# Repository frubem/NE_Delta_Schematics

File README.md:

# Nuova Elettronica DELTA computer - Redux

## DISCLAIMER

Any use of this project is **under your own responsibility**.
By using this project You will agree that I cannot be held responsible if it will destroy any of your devices, damage your computer, burn down your house or whatever.

### Sponsorship

This project is sponsored by [PCBWay](https://pcbway.com).
PCBWay specializes in manufacturing high-quality PCBs and makes them affordable to hobbyist and professionals alike.

The range of services they offer include PCB prototyping, assembly, instant quotes for your order, a verification process by a team
of experts and an easy to use, hassle-free order process.

I'm grateful to PCBWay for their support in developing this board. It was invaluable, and, thanks to them and thanks to the people that supported me, I was able to push this forward and create the first revision of the DELTA Redux!

## Introduction

This repository contains a recreation of the schematics and PCBs for the DELTA computer, an Apple IIe clone by Nuova Elettronica.

The schematics have been reconstructed starting from the originals found in the Nuova Elettronica magazine (scans included in the repository)
and have been corrected comparing them to scans of the original PCBs, while a new PCB was redrawn.

The files in the `PLDs_ROMs` directory have been provided by Roberto Bazzano, that also uploaded all the available documentation about the DELTA [on his website](https://www.z80ne.com/delta).
His page includes the original schematic scanned from the magazine, the EPROM/PLD dumps, gerbers for two of the boards plus high resolution scans of the PCBs.

This project aims at the following:
1. Recreate the schematics of the main DELTA boards, so they are searchable and easier to use for troubleshooting
2. Rebuild the PCBs using KiCAD, possibly using footprints for easier to find connectors and transistors, and to allow further modifications of the project should someone wish to do so

**Many thanks to Roberto** because, without him, all the effort in recreating the schematics would have been moot!

### Compatibility

The [original article](Docs/delta_computer.pdf) by Nuova Elettronica touts "perfect compatibility with APPLE 2 and APPLE 2E", but I've found out that this is not really the case.

You can reference [this file](Apple2e_differences.md) for differences (and fixes) I found when comparing to an Apple IIe.

Also, note that this clone, by default, boots in 50Hz mode. 60Hz mode can be obtained by properly setting up the CRTC. I have prepared a modified EP780/A ROM for this, you can find it [here](PLDs_ROMs/DELTA_Mainboard/mod/EP780A_60hz.BIN).

Getting the //e enhanced ROMs to work was also easy enough, as it was sufficient to add the CRTC initialization code and the call to it. Note that the VIDEO ROM was not ported over, as the organization of that
ROM on the delta is totally different. Given that I actually plan to evolve this computer using an A2DVI as video circuitry, this should be a non-issue.

### Support

If you wish to support me in building new hardware and software for old machines, [throw a few euros in my direction via Ko-Fi](https://ko-fi.com/hkzlab) ☕!

## Build one!

### Order the PCBs

You can find the gerbers in this repository, or you can order the PCBs at **PCBWay!**

Note that you will need, at least, the motherboard (LX780) and one of the video modules. The keyboard is currently work in progress.

- [LX780](https://www.pcbway.com/project/shareproject/DELTA_Redux_Apple_IIe_clone_dc32412e.html), the motherboard
- [LX782](https://www.pcbway.com/project/shareproject/DELTA_Redux_Composite_TV_Video_card_8b8ff858.html), monochrome composite/VHF video output
- [LX783](https://www.pcbway.com/project/shareproject/DELTA_Redux_RGB_Video_card_4a65742e.html), analog RGB video output

### Fixes

Every board directory contains a `fixes.md` file detailing the fix to apply to each revision of the boards:

- [LX780](LX780_Delta-original/fixes.md)
- [LX782](LX782_Monochrome_Video/fixes.md)
- LX783

### Bill of Material

Every board directory contains a `bom.md` file containing the bill of material for the card.

- [LX780](LX780_Delta-original/bom.md)
- [LX782](LX782_Monochrome_Video/bom.md)
- [LX783](LX783_RGB_Video/bom.md)

## TODO

- Explore the functional differences with an original Apple IIe
- Build a keyboard
- Build a case
- Investigate replacing the video circuitry with an embedded A2DVI board
- Test cassette IN/OUT
- Modify //e enhanced ROMs self test to match behavior of DELTA ROMs

## Thanks

- [Roberto Bazzano](https://www.z80ne.com/) for the photos and PLD dumps
- [DosFox](https://tech.lgbt/@DosFox) for the support

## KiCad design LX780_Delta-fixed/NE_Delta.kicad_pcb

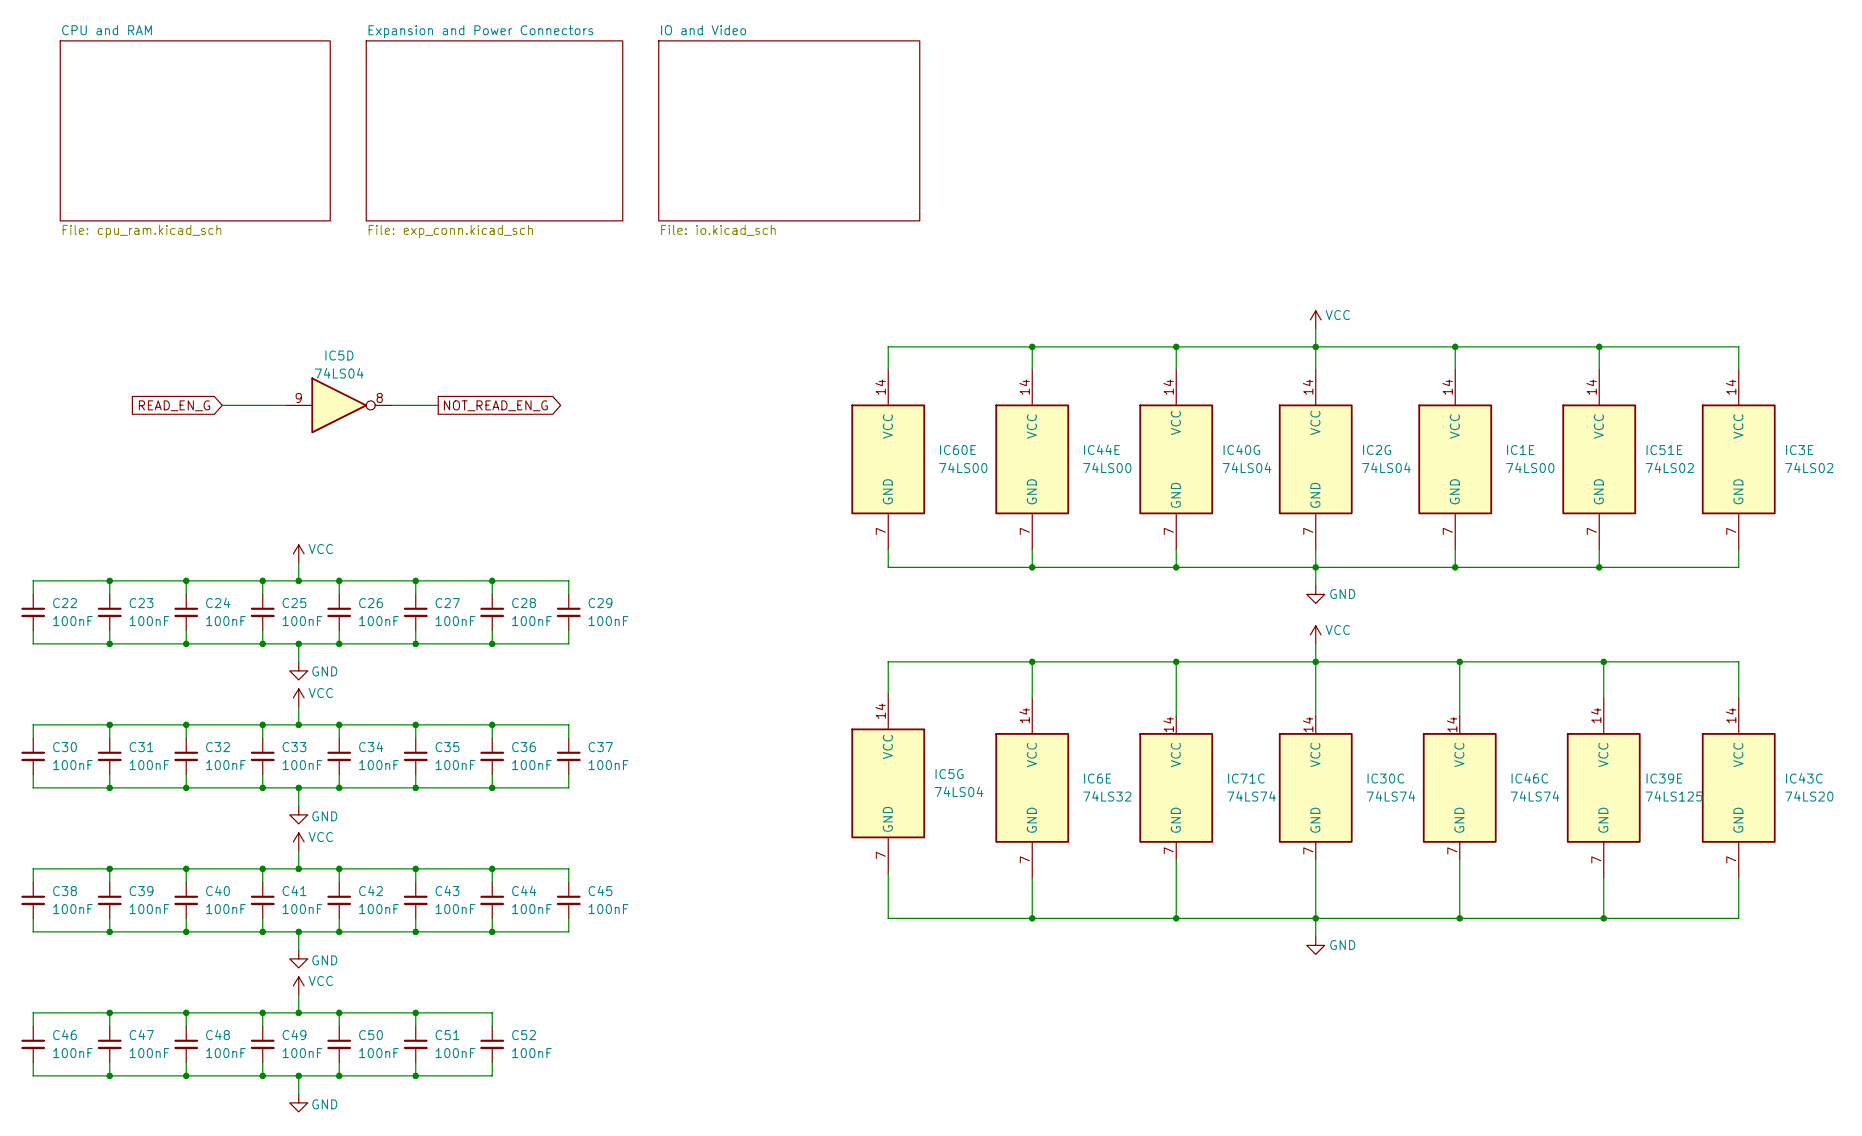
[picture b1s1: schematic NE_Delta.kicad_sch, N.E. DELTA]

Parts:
C22, C23, C24, C25, C26, C27, C28, C29, C30, C31, C32, C33, C34, C35, C36, C37, C38, C39, C40, C41, C42, C43, C44, C45, C46, C47, C48, C49, C50, C51, C52: 100nF; C_Disc_D6.0mm_W2.5mm_P5.00mm
IC1, IC44, IC60: 74LS00; DIP-14_W7.62mm
IC2, IC5, IC40: 74LS04; DIP-14_W7.62mm
IC3, IC51: 74LS02; DIP-14_W7.62mm
IC6: 74LS32; DIP-14_W7.62mm
IC30, IC46, IC71: 74LS74; DIP-14_W7.62mm
IC39: 74LS125; DIP-14_W7.62mm
IC43: 74LS20; DIP-14_W7.62mm

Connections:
+5V: C22.1, C23.1, C24.1, C25.1, C26.1, C27.1, C28.1, C29.1, C30.1, C31.1, C32.1, C33.1, C34.1, C35.1, C36.1, C37.1, C38.1, C39.1, C40.1, C41.1, C42.1, C43.1, C44.1, C45.1, C46.1, C47.1, C48.1, C49.1, C50.1, C51.1, C52.1, IC1.14 (VCC), IC2.14 (VCC), IC3.14 (VCC), IC5.14 (VCC), IC6.14 (VCC), IC30.14 (VCC), IC39.14 (VCC), IC40.14 (VCC), IC43.14 (VCC), IC44.14 (VCC), IC46.14 (VCC), IC51.14 (VCC), IC60.14 (VCC), IC71.14 (VCC); also elsewhere on the board
GND: C22.2, C23.2, C24.2, C25.2, C26.2, C27.2, C28.2, C29.2, C30.2, C31.2, C32.2, C33.2, C34.2, C35.2, C36.2, C37.2, C38.2, C39.2, C40.2, C41.2, C42.2, C43.2, C44.2, C45.2, C46.2, C47.2, C48.2, C49.2, C50.2, C51.2, C52.2, IC1.7 (GND), IC2.7 (GND), IC3.7 (GND), IC5.7 (GND), IC6.7 (GND), IC30.7 (GND), IC39.7 (GND), IC40.7 (GND), IC43.7 (GND), IC44.7 (GND), IC46.7 (GND), IC51.7 (GND), IC60.7 (GND), IC71.7 (GND); also elsewhere on the board
unnamed 261: IC5.8; also elsewhere on the board

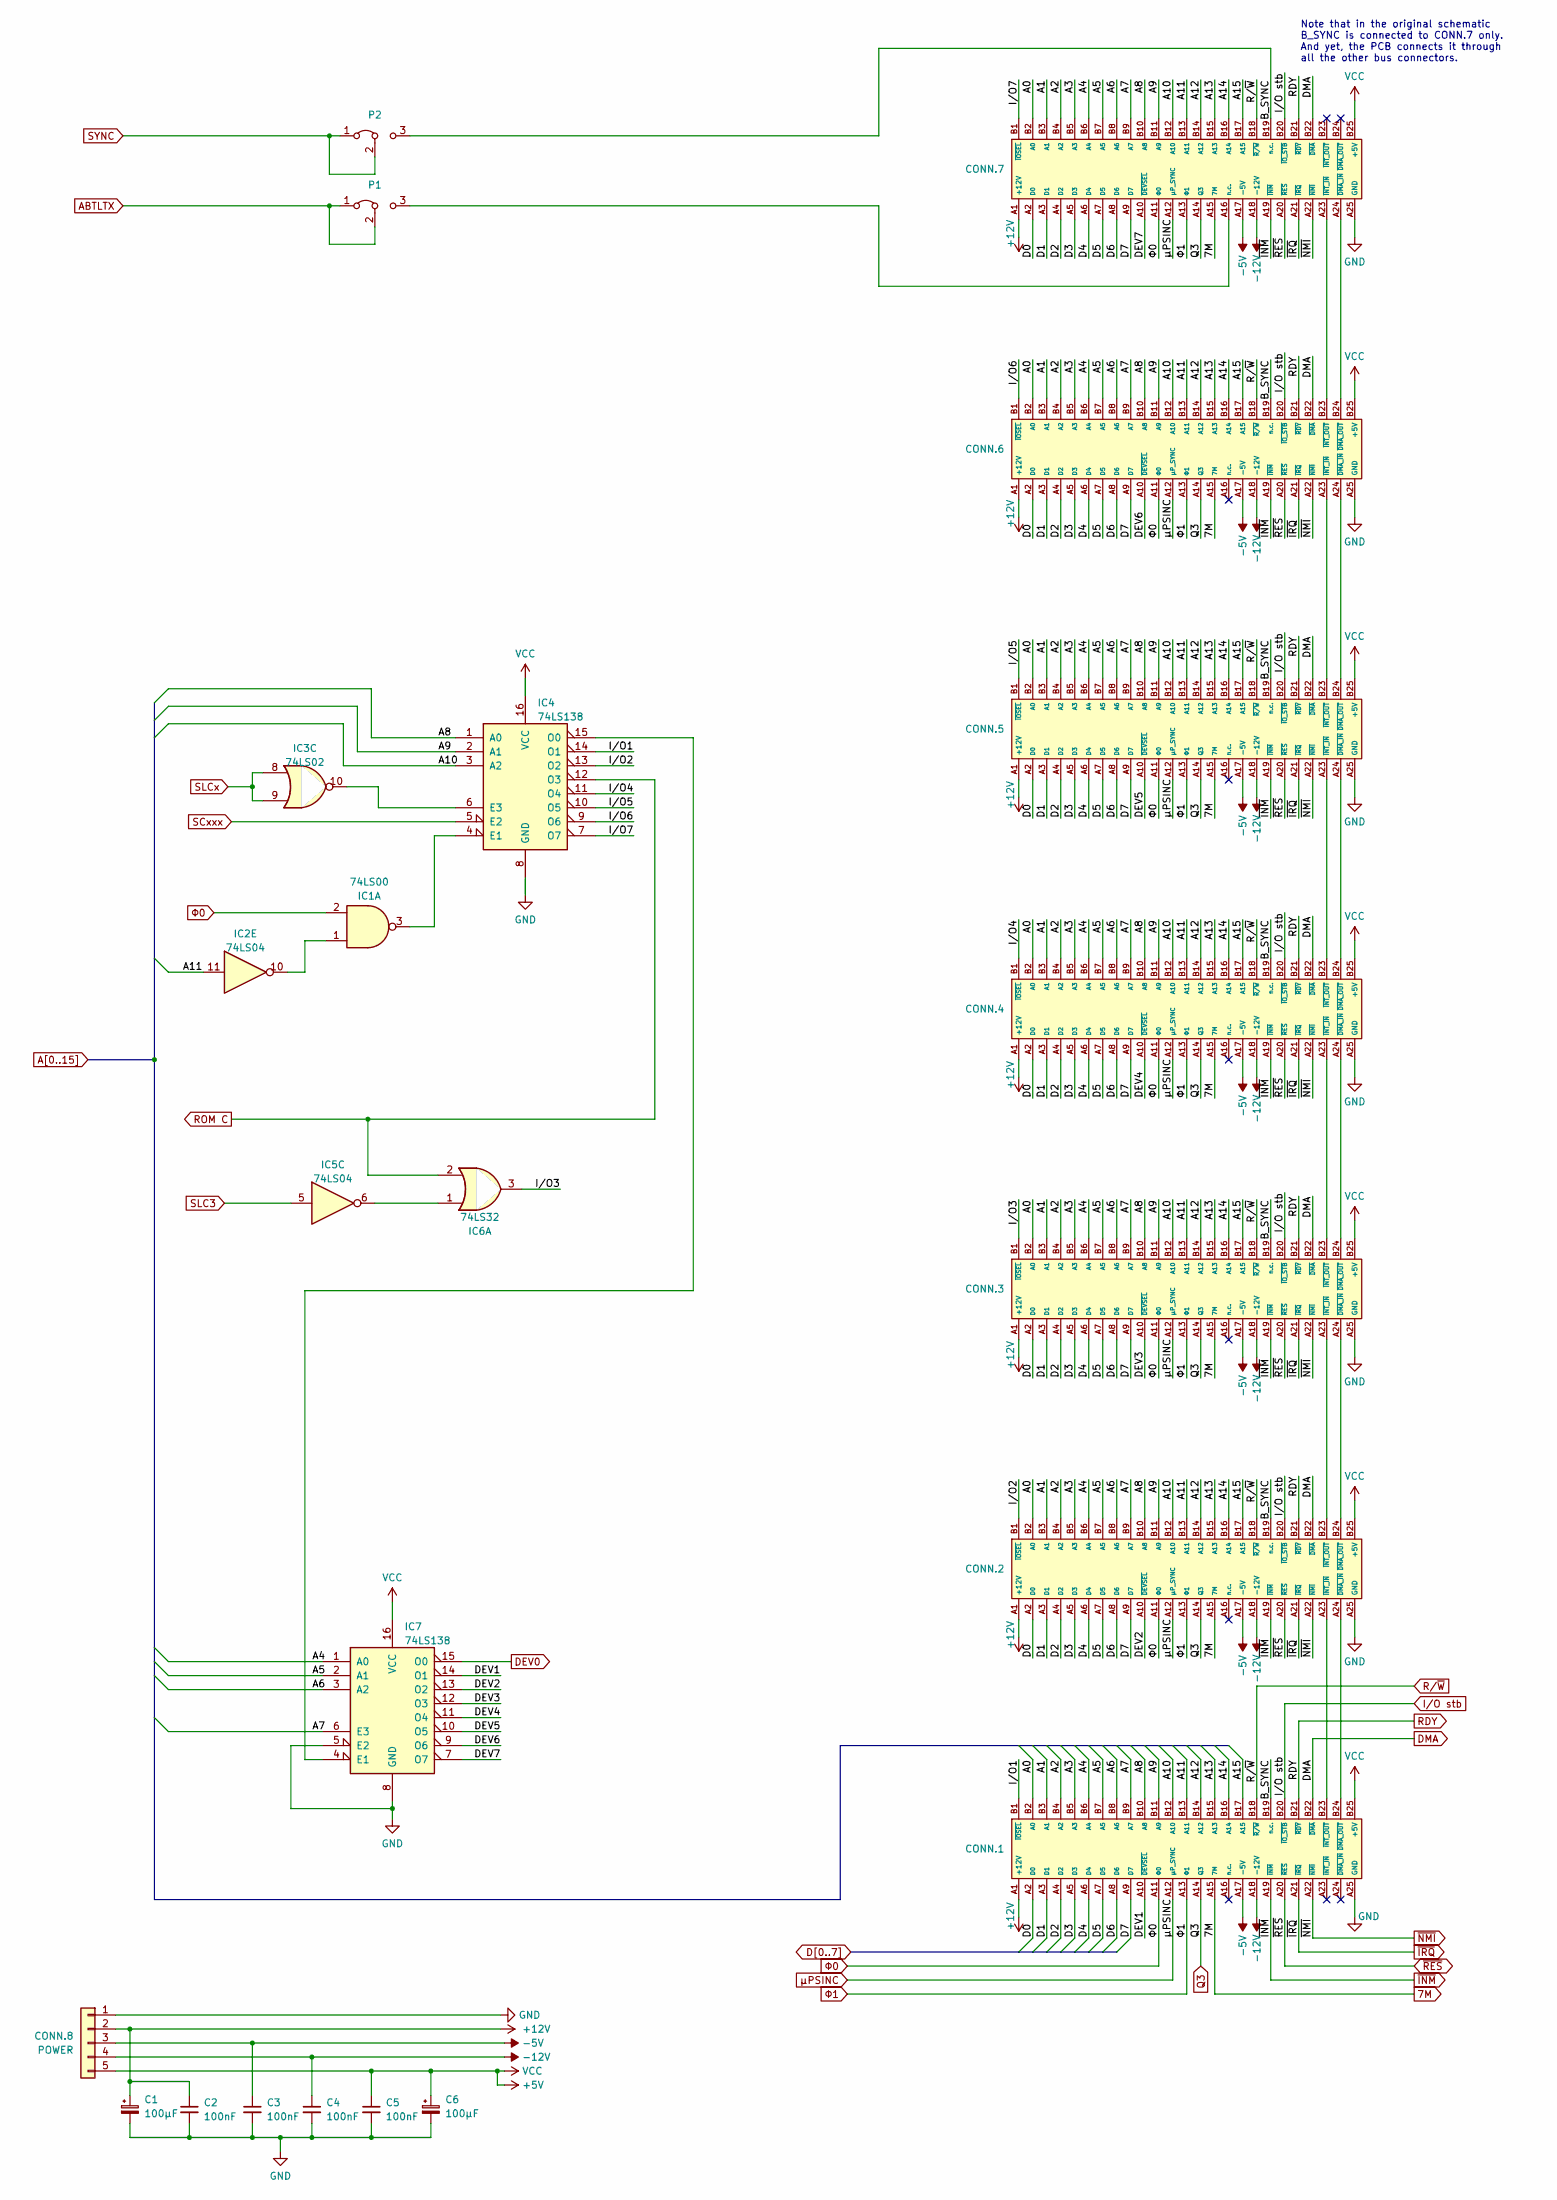
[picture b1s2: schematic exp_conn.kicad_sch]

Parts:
C1, C6: 100μF; CP_Radial_D8.0mm_P5.00mm
C2, C3, C4, C5: 100nF; C_Disc_D6.0mm_W2.5mm_P5.00mm
CONN.1, CONN.2, CONN.3, CONN.4, CONN.5, CONN.6: NE_BUS
CONN.7: NE_BUS_halfsilk
CONN.8: POWER; NE_POWER
IC1: 74LS00; DIP-14_W7.62mm
IC2, IC5: 74LS04; DIP-14_W7.62mm
IC3: 74LS02; DIP-14_W7.62mm
IC4, IC7: 74LS138; DIP-16_W7.62mm
IC6: 74LS32; DIP-14_W7.62mm
P1, P2: Jumper_3_Bridged12; PinHeader_1x03_P2.54mm_Vertical

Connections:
7M: CONN.1.A15 (7M), CONN.2.A15 (7M), CONN.3.A15 (7M), CONN.4.A15 (7M), CONN.5.A15 (7M), CONN.6.A15 (7M), CONN.7.A15 (7M); also elsewhere on the board
+5V: C5.1, C6.1, CONN.1.B25 (+5V), CONN.2.B25 (+5V), CONN.3.B25 (+5V), CONN.4.B25 (+5V), CONN.5.B25 (+5V), CONN.6.B25 (+5V), CONN.7.B25 (+5V), CONN.8.5, IC4.16 (VCC), IC7.16 (VCC); also elsewhere on the board
+12V: C1.1, C2.1, CONN.1.A1 (+12V), CONN.2.A1 (+12V), CONN.3.A1 (+12V), CONN.4.A1 (+12V), CONN.5.A1 (+12V), CONN.6.A1 (+12V), CONN.7.A1 (+12V), CONN.8.2; also elsewhere on the board
-5V: C3.1, CONN.1.A17 (-5V), CONN.2.A17 (-5V), CONN.3.A17 (-5V), CONN.4.A17 (-5V), CONN.5.A17 (-5V), CONN.6.A17 (-5V), CONN.7.A17 (-5V), CONN.8.3; also elsewhere on the board
-12V: C4.1, CONN.1.A18 (-12V), CONN.2.A18 (-12V), CONN.3.A18 (-12V), CONN.4.A18 (-12V), CONN.5.A18 (-12V), CONN.6.A18 (-12V), CONN.7.A18 (-12V), CONN.8.4; also elsewhere on the board
/Expansion and Power Connectors/B_SYNC: CONN.1.B19 (n.c.), CONN.2.B19 (n.c.), CONN.3.B19 (n.c.), CONN.4.B19 (n.c.), CONN.5.B19 (n.c.), CONN.6.B19 (n.c.), CONN.7.B19 (n.c.), P2.3 (B)
/Expansion and Power Connectors/DEV1: CONN.1.A10 (~DEVSEL), IC7.14 (O1)
/Expansion and Power Connectors/DEV2: CONN.2.A10 (~DEVSEL), IC7.13 (O2)
/Expansion and Power Connectors/DEV3: CONN.3.A10 (~DEVSEL), IC7.12 (O3)
/Expansion and Power Connectors/DEV4: CONN.4.A10 (~DEVSEL), IC7.11 (O4)
/Expansion and Power Connectors/DEV5: CONN.5.A10 (~DEVSEL), IC7.10 (O5)
/Expansion and Power Connectors/DEV6: CONN.6.A10 (~DEVSEL), IC7.9 (O6)
/Expansion and Power Connectors/DEV7: CONN.7.A10 (~DEVSEL), IC7.7 (O7)
/Expansion and Power Connectors/I/O1: CONN.1.B1 (~IOSEL), IC4.14 (O1)
/Expansion and Power Connectors/I/O2: CONN.2.B1 (~IOSEL), IC4.13 (O2)
/Expansion and Power Connectors/I/O3: CONN.3.B1 (~IOSEL), IC6.3
/Expansion and Power Connectors/I/O4: CONN.4.B1 (~IOSEL), IC4.11 (O4)
/Expansion and Power Connectors/I/O5: CONN.5.B1 (~IOSEL), IC4.10 (O5)
/Expansion and Power Connectors/I/O6: CONN.6.B1 (~IOSEL), IC4.9 (O6)
/Expansion and Power Connectors/I/O7: CONN.7.B1 (~IOSEL), IC4.7 (O7)
A0: CONN.1.B2 (A0), CONN.2.B2 (A0), CONN.3.B2 (A0), CONN.4.B2 (A0), CONN.5.B2 (A0), CONN.6.B2 (A0), CONN.7.B2 (A0); also elsewhere on the board
A1: CONN.1.B3 (A1), CONN.2.B3 (A1), CONN.3.B3 (A1), CONN.4.B3 (A1), CONN.5.B3 (A1), CONN.6.B3 (A1), CONN.7.B3 (A1); also elsewhere on the board
A2: CONN.1.B4 (A2), CONN.2.B4 (A2), CONN.3.B4 (A2), CONN.4.B4 (A2), CONN.5.B4 (A2), CONN.6.B4 (A2), CONN.7.B4 (A2); also elsewhere on the board
A3: CONN.1.B5 (A3), CONN.2.B5 (A3), CONN.3.B5 (A3), CONN.4.B5 (A3), CONN.5.B5 (A3), CONN.6.B5 (A3), CONN.7.B5 (A3); also elsewhere on the board
A4: CONN.1.B6 (A4), CONN.2.B6 (A4), CONN.3.B6 (A4), CONN.4.B6 (A4), CONN.5.B6 (A4), CONN.6.B6 (A4), CONN.7.B6 (A4), IC7.1 (A0); also elsewhere on the board
A5: CONN.1.B7 (A5), CONN.2.B7 (A5), CONN.3.B7 (A5), CONN.4.B7 (A5), CONN.5.B7 (A5), CONN.6.B7 (A5), CONN.7.B7 (A5), IC7.2 (A1); also elsewhere on the board
A6: CONN.1.B8 (A6), CONN.2.B8 (A6), CONN.3.B8 (A6), CONN.4.B8 (A6), CONN.5.B8 (A6), CONN.6.B8 (A6), CONN.7.B8 (A6), IC7.3 (A2); also elsewhere on the board
A7: CONN.1.B9 (A7), CONN.2.B9 (A7), CONN.3.B9 (A7), CONN.4.B9 (A7), CONN.5.B9 (A7), CONN.6.B9 (A7), CONN.7.B9 (A7), IC7.6 (E3); also elsewhere on the board
A8: CONN.1.B10 (A8), CONN.2.B10 (A8), CONN.3.B10 (A8), CONN.4.B10 (A8), CONN.5.B10 (A8), CONN.6.B10 (A8), CONN.7.B10 (A8), IC4.1 (A0); also elsewhere on the board
A9: CONN.1.B11 (A9), CONN.2.B11 (A9), CONN.3.B11 (A9), CONN.4.B11 (A9), CONN.5.B11 (A9), CONN.6.B11 (A9), CONN.7.B11 (A9), IC4.2 (A1); also elsewhere on the board
A10: CONN.1.B12 (A10), CONN.2.B12 (A10), CONN.3.B12 (A10), CONN.4.B12 (A10), CONN.5.B12 (A10), CONN.6.B12 (A10), CONN.7.B12 (A10), IC4.3 (A2); also elsewhere on the board
A11: CONN.1.B13 (A11), CONN.2.B13 (A11), CONN.3.B13 (A11), CONN.4.B13 (A11), CONN.5.B13 (A11), CONN.6.B13 (A11), CONN.7.B13 (A11), IC2.11; also elsewhere on the board
A12: CONN.1.B14 (A12), CONN.2.B14 (A12), CONN.3.B14 (A12), CONN.4.B14 (A12), CONN.5.B14 (A12), CONN.6.B14 (A12), CONN.7.B14 (A12); also elsewhere on the board
A13: CONN.1.B15 (A13), CONN.2.B15 (A13), CONN.3.B15 (A13), CONN.4.B15 (A13), CONN.5.B15 (A13), CONN.6.B15 (A13), CONN.7.B15 (A13); also elsewhere on the board
A14: CONN.1.B16 (A14), CONN.2.B16 (A14), CONN.3.B16 (A14), CONN.4.B16 (A14), CONN.5.B16 (A14), CONN.6.B16 (A14), CONN.7.B16 (A14); also elsewhere on the board
A15: CONN.1.B17 (A15), CONN.2.B17 (A15), CONN.3.B17 (A15), CONN.4.B17 (A15), CONN.5.B17 (A15), CONN.6.B17 (A15), CONN.7.B17 (A15); also elsewhere on the board
ABTLTX: P1.1 (A), P1.2 (C); also elsewhere on the board
D0: CONN.1.A2 (D0), CONN.2.A2 (D0), CONN.3.A2 (D0), CONN.4.A2 (D0), CONN.5.A2 (D0), CONN.6.A2 (D0), CONN.7.A2 (D0); also elsewhere on the board
D1: CONN.1.A3 (D1), CONN.2.A3 (D1), CONN.3.A3 (D1), CONN.4.A3 (D1), CONN.5.A3 (D1), CONN.6.A3 (D1), CONN.7.A3 (D1); also elsewhere on the board
D2: CONN.1.A4 (D2), CONN.2.A4 (D2), CONN.3.A4 (D2), CONN.4.A4 (D2), CONN.5.A4 (D2), CONN.6.A4 (D2), CONN.7.A4 (D2); also elsewhere on the board
D3: CONN.1.A5 (D3), CONN.2.A5 (D3), CONN.3.A5 (D3), CONN.4.A5 (D3), CONN.5.A5 (D3), CONN.6.A5 (D3), CONN.7.A5 (D3); also elsewhere on the board
D4: CONN.1.A6 (D4), CONN.2.A6 (D4), CONN.3.A6 (D4), CONN.4.A6 (D4), CONN.5.A6 (D4), CONN.6.A6 (D4), CONN.7.A6 (D4); also elsewhere on the board
D5: CONN.1.A7 (D5), CONN.2.A7 (D5), CONN.3.A7 (D5), CONN.4.A7 (D5), CONN.5.A7 (D5), CONN.6.A7 (D5), CONN.7.A7 (D5); also elsewhere on the board
D6: CONN.1.A8 (D6), CONN.2.A8 (D6), CONN.3.A8 (D6), CONN.4.A8 (D6), CONN.5.A8 (D6), CONN.6.A8 (D6), CONN.7.A8 (D6); also elsewhere on the board
D7: CONN.1.A9 (D7), CONN.2.A9 (D7), CONN.3.A9 (D7), CONN.4.A9 (D7), CONN.5.A9 (D7), CONN.6.A9 (D7), CONN.7.A9 (D7); also elsewhere on the board
DEV0: IC7.15 (O0); also elsewhere on the board
DMA: CONN.1.B22 (~DMA), CONN.2.B22 (~DMA), CONN.3.B22 (~DMA), CONN.4.B22 (~DMA), CONN.5.B22 (~DMA), CONN.6.B22 (~DMA), CONN.7.B22 (~DMA); also elsewhere on the board
GND: C1.2, C2.2, C3.2, C4.2, C5.2, C6.2, CONN.1.A25 (GND), CONN.2.A25 (GND), CONN.3.A25 (GND), CONN.4.A25 (GND), CONN.5.A25 (GND), CONN.6.A25 (GND), CONN.7.A25 (GND), CONN.8.1, IC4.8 (GND), IC7.5 (E2), IC7.8 (GND); also elsewhere on the board
I/O stb: CONN.1.B20 (~IO_STB), CONN.2.B20 (~IO_STB), CONN.3.B20 (~IO_STB), CONN.4.B20 (~IO_STB), CONN.5.B20 (~IO_STB), CONN.6.B20 (~IO_STB), CONN.7.B20 (~IO_STB); also elsewhere on the board
unnamed: CONN.1.B24 (~DMA_OUT), CONN.2.A24 (~DMA_IN)
unnamed: CONN.1.B23 (~INT_OUT), CONN.2.A23 (~INT_IN)
unnamed: CONN.2.B24 (~DMA_OUT), CONN.3.A24 (~DMA_IN)
unnamed: CONN.2.B23 (~INT_OUT), CONN.3.A23 (~INT_IN)
unnamed: CONN.3.B24 (~DMA_OUT), CONN.4.A24 (~DMA_IN)
unnamed: CONN.3.B23 (~INT_OUT), CONN.4.A23 (~INT_IN)
unnamed: CONN.4.B24 (~DMA_OUT), CONN.5.A24 (~DMA_IN)
unnamed: CONN.4.B23 (~INT_OUT), CONN.5.A23 (~INT_IN)
unnamed: CONN.5.B24 (~DMA_OUT), CONN.6.A24 (~DMA_IN)
unnamed: CONN.5.B23 (~INT_OUT), CONN.6.A23 (~INT_IN)
unnamed: CONN.6.B24 (~DMA_OUT), CONN.7.A24 (~DMA_IN)
unnamed: CONN.6.B23 (~INT_OUT), CONN.7.A23 (~INT_IN)
unnamed: IC1.1, IC2.10
unnamed: IC1.3, IC4.4 (E1)
unnamed: IC3.10, IC4.6 (E3)
unnamed: IC4.15 (O0), IC7.4 (E1)
unnamed: IC5.6, IC6.1
unnamed: CONN.7.A16 (n.c.), P1.3 (B)
Q3: CONN.1.A14 (Q3), CONN.2.A14 (Q3), CONN.3.A14 (Q3), CONN.4.A14 (Q3), CONN.5.A14 (Q3), CONN.6.A14 (Q3), CONN.7.A14 (Q3); also elsewhere on the board
RDY: CONN.1.B21 (~RDY), CONN.2.B21 (~RDY), CONN.3.B21 (~RDY), CONN.4.B21 (~RDY), CONN.5.B21 (~RDY), CONN.6.B21 (~RDY), CONN.7.B21 (~RDY); also elsewhere on the board
ROM C: IC4.12 (O3), IC6.2; also elsewhere on the board
R/~W: CONN.1.B18 (~R/W), CONN.2.B18 (~R/W), CONN.3.B18 (~R/W), CONN.4.B18 (~R/W), CONN.5.B18 (~R/W), CONN.6.B18 (~R/W), CONN.7.B18 (~R/W); also elsewhere on the board
SCxxx: IC4.5 (E2); also elsewhere on the board
SLC3: IC5.5; also elsewhere on the board
SLCx: IC3.8, IC3.9; also elsewhere on the board
SYNC: P2.1 (A), P2.2 (C); also elsewhere on the board
~INM: CONN.1.A19 (~INM), CONN.2.A19 (~INM), CONN.3.A19 (~INM), CONN.4.A19 (~INM), CONN.5.A19 (~INM), CONN.6.A19 (~INM), CONN.7.A19 (~INM); also elsewhere on the board
~IRQ: CONN.1.A21 (~IRQ), CONN.2.A21 (~IRQ), CONN.3.A21 (~IRQ), CONN.4.A21 (~IRQ), CONN.5.A21 (~IRQ), CONN.6.A21 (~IRQ), CONN.7.A21 (~IRQ); also elsewhere on the board
~NMI: CONN.1.A22 (~NMI), CONN.2.A22 (~NMI), CONN.3.A22 (~NMI), CONN.4.A22 (~NMI), CONN.5.A22 (~NMI), CONN.6.A22 (~NMI), CONN.7.A22 (~NMI); also elsewhere on the board
~RES: CONN.1.A20 (~RES), CONN.2.A20 (~RES), CONN.3.A20 (~RES), CONN.4.A20 (~RES), CONN.5.A20 (~RES), CONN.6.A20 (~RES), CONN.7.A20 (~RES); also elsewhere on the board
Φ0: CONN.1.A11 (Φ0), CONN.2.A11 (Φ0), CONN.3.A11 (Φ0), CONN.4.A11 (Φ0), CONN.5.A11 (Φ0), CONN.6.A11 (Φ0), CONN.7.A11 (Φ0), IC1.2; also elsewhere on the board
Φ1: CONN.1.A13 (Φ1), CONN.2.A13 (Φ1), CONN.3.A13 (Φ1), CONN.4.A13 (Φ1), CONN.5.A13 (Φ1), CONN.6.A13 (Φ1), CONN.7.A13 (Φ1); also elsewhere on the board
μPSINC: CONN.1.A12 (μP_SYNC), CONN.2.A12 (μP_SYNC), CONN.3.A12 (μP_SYNC), CONN.4.A12 (μP_SYNC), CONN.5.A12 (μP_SYNC), CONN.6.A12 (μP_SYNC), CONN.7.A12 (μP_SYNC); also elsewhere on the board

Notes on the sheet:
Note that in the original schematic B_SYNC is connected to CONN.7 only. And yet, the PCB connects it through all the other bus connectors.
